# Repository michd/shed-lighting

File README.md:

# Shed Lighting

Cloned from my [Monitor Backlights](https://github.com/michd/monitor-backlights), as I figured it'd be a good starting point. In this instance, I'll have a single board of 5x5 10mm white LEDS, and I'll also design a 3D-printable
case for it. Probably to run on a 6V battery.

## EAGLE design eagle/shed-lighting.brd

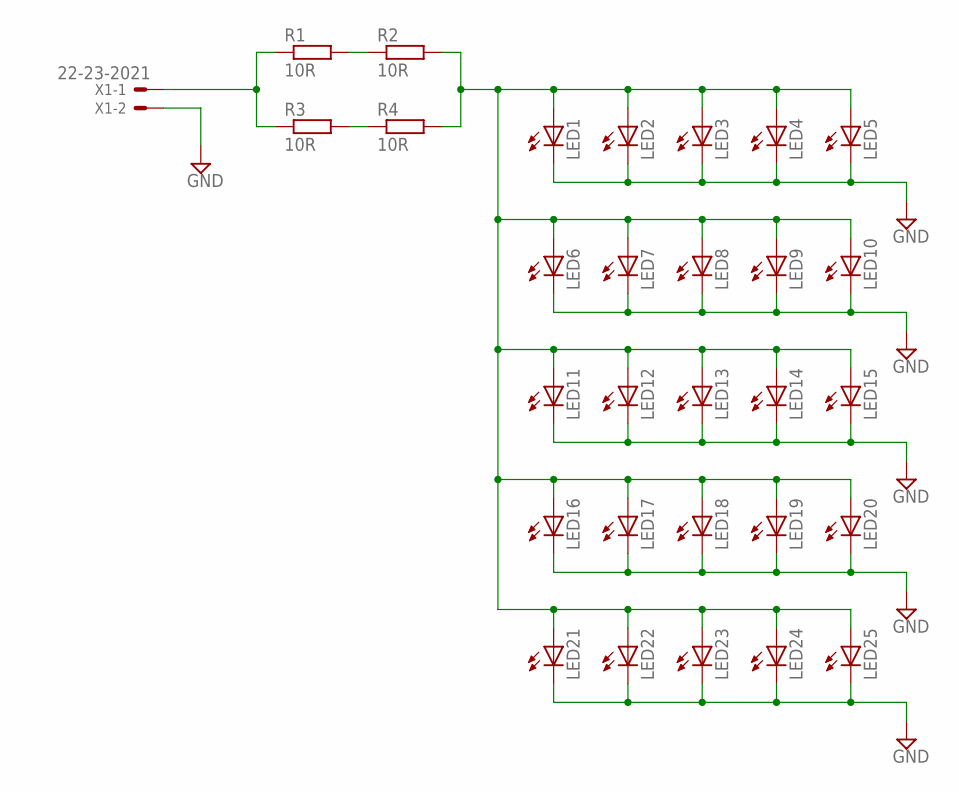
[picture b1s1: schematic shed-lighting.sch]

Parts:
LED1, LED2, LED3, LED4, LED5, LED6, LED7, LED8, LED9, LED10, LED11, LED12, LED13, LED14, LED15, LED16, LED17, LED18, LED19, LED20, LED21, LED22, LED23, LED24, LED25: LED10MM
R1, R2, R3, R4: 10R; 0207/10
X1: 22-23-2021

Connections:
GND: LED1.K (C), LED2.K (C), LED3.K (C), LED4.K (C), LED5.K (C), LED6.K (C), LED7.K (C), LED8.K (C), LED9.K (C), LED10.K (C), LED11.K (C), LED12.K (C), LED13.K (C), LED14.K (C), LED15.K (C), LED16.K (C), LED17.K (C), LED18.K (C), LED19.K (C), LED20.K (C), LED21.K (C), LED22.K (C), LED23.K (C), LED24.K (C), LED25.K (C), X1.2
unnamed: R1.2, R2.1
unnamed: R3.2, R4.1
unnamed: LED1.A, LED2.A, LED3.A, LED4.A, LED5.A, LED6.A, LED7.A, LED8.A, LED9.A, LED10.A, LED11.A, LED12.A, LED13.A, LED14.A, LED15.A, LED16.A, LED17.A, LED18.A, LED19.A, LED20.A, LED21.A, LED22.A, LED23.A, LED24.A, LED25.A, R2.2, R4.2
unnamed: R1.1, R3.1, X1.1

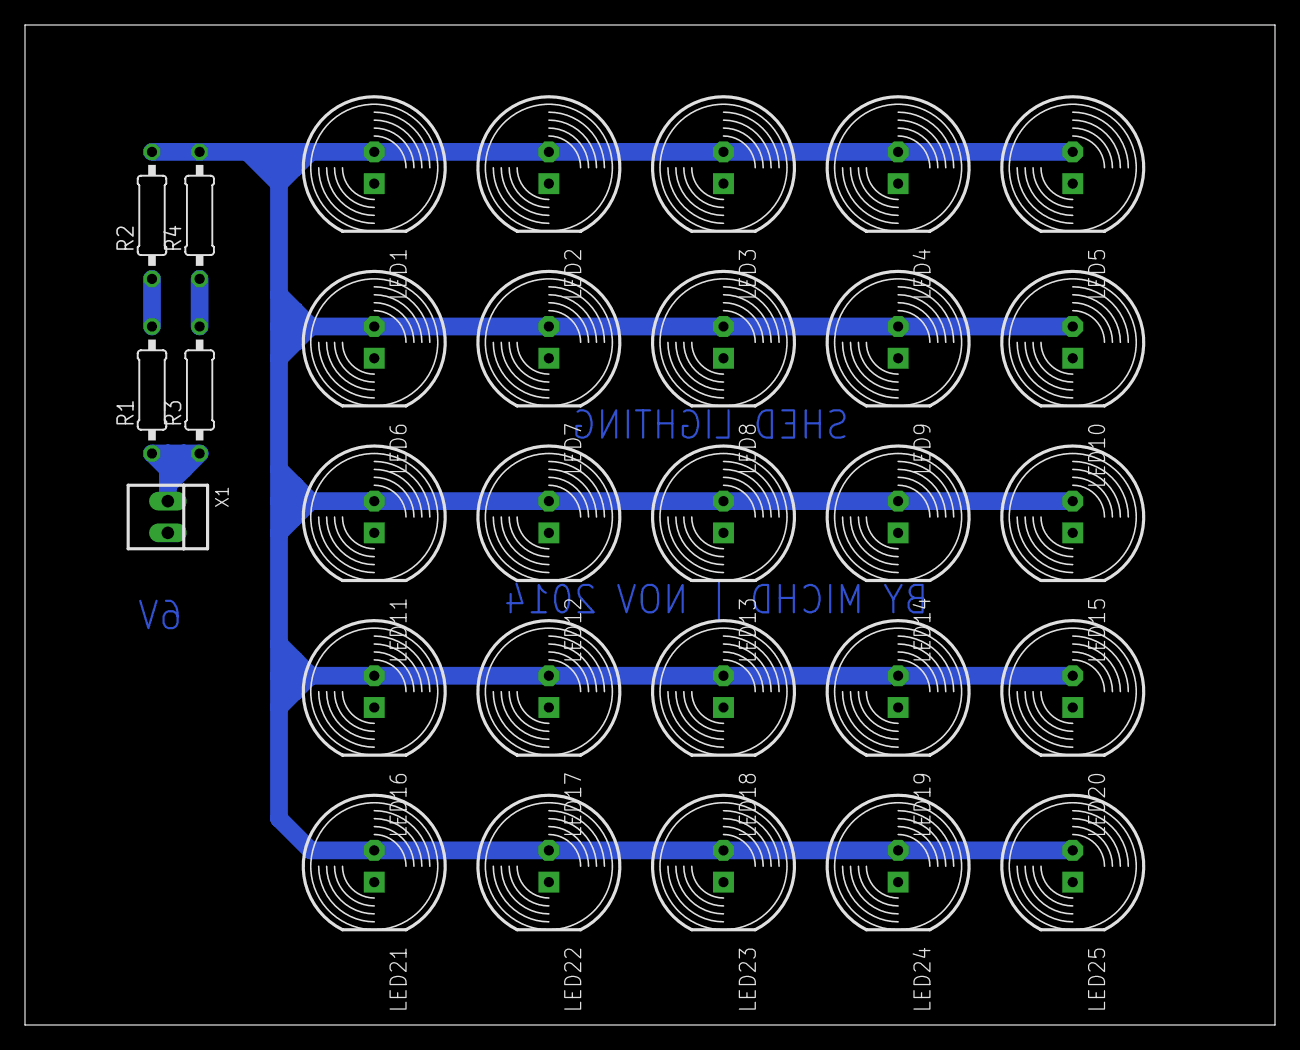
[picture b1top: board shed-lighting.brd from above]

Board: 2 copper layers, 100.0 x 80.0 mm, 30 parts (0 on the bottom side), 5 nets.

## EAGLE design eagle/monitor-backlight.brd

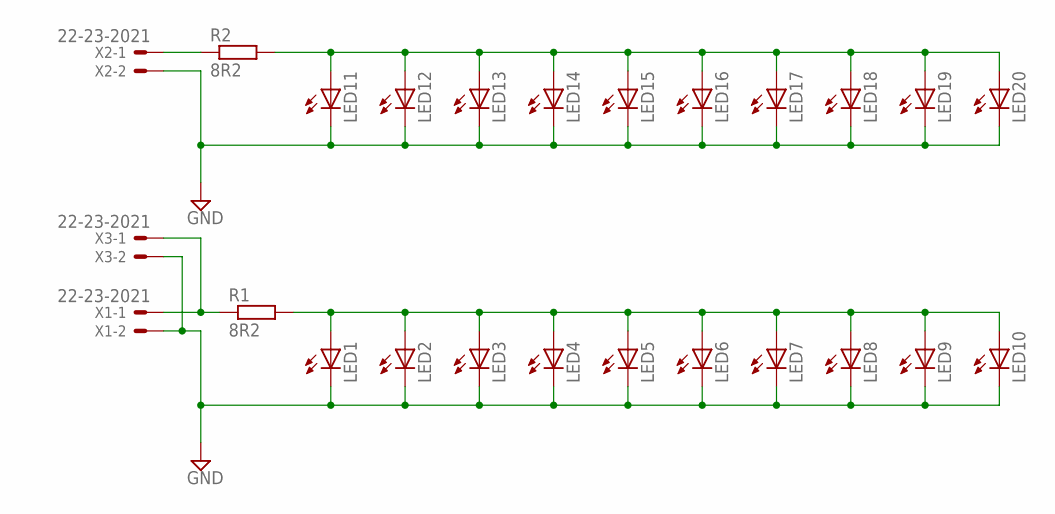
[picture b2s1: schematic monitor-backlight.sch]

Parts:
LED1, LED2, LED3, LED4, LED5, LED6, LED7, LED8, LED9, LED10, LED11, LED12, LED13, LED14, LED15, LED16, LED17, LED18, LED19, LED20: LED10MM
R1, R2: 8R2; 0204/7
X1, X2, X3: 22-23-2021

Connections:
GND: LED1.K (C), LED2.K (C), LED3.K (C), LED4.K (C), LED5.K (C), LED6.K (C), LED7.K (C), LED8.K (C), LED9.K (C), LED10.K (C), LED11.K (C), LED12.K (C), LED13.K (C), LED14.K (C), LED15.K (C), LED16.K (C), LED17.K (C), LED18.K (C), LED19.K (C), LED20.K (C), X1.2, X2.2, X3.2
unnamed: LED1.A, LED2.A, LED3.A, LED4.A, LED5.A, LED6.A, LED7.A, LED8.A, LED9.A, LED10.A, R1.2
unnamed: LED11.A, LED12.A, LED13.A, LED14.A, LED15.A, LED16.A, LED17.A, LED18.A, LED19.A, LED20.A, R2.2
unnamed: R2.1, X2.1
unnamed: R1.1, X1.1, X3.1

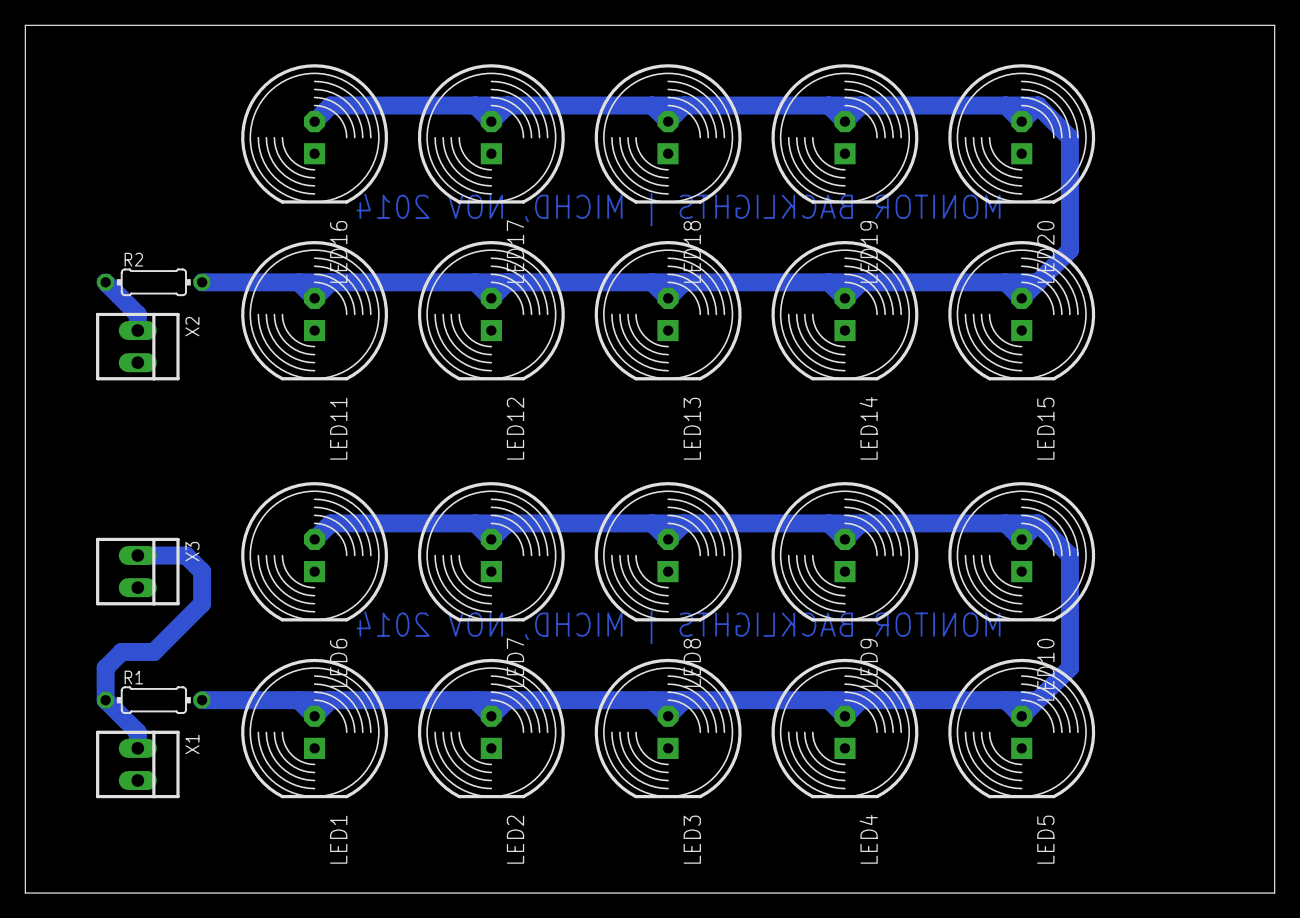
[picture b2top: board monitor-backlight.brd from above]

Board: 2 copper layers, 98.7 x 68.6 mm, 25 parts (0 on the bottom side), 5 nets.

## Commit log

2014-11-02 Update readme for shed-lighting
2014-11-02 Design schematic and board
2014-11-02 Update screenshot
2014-11-07 Design case in openscad
